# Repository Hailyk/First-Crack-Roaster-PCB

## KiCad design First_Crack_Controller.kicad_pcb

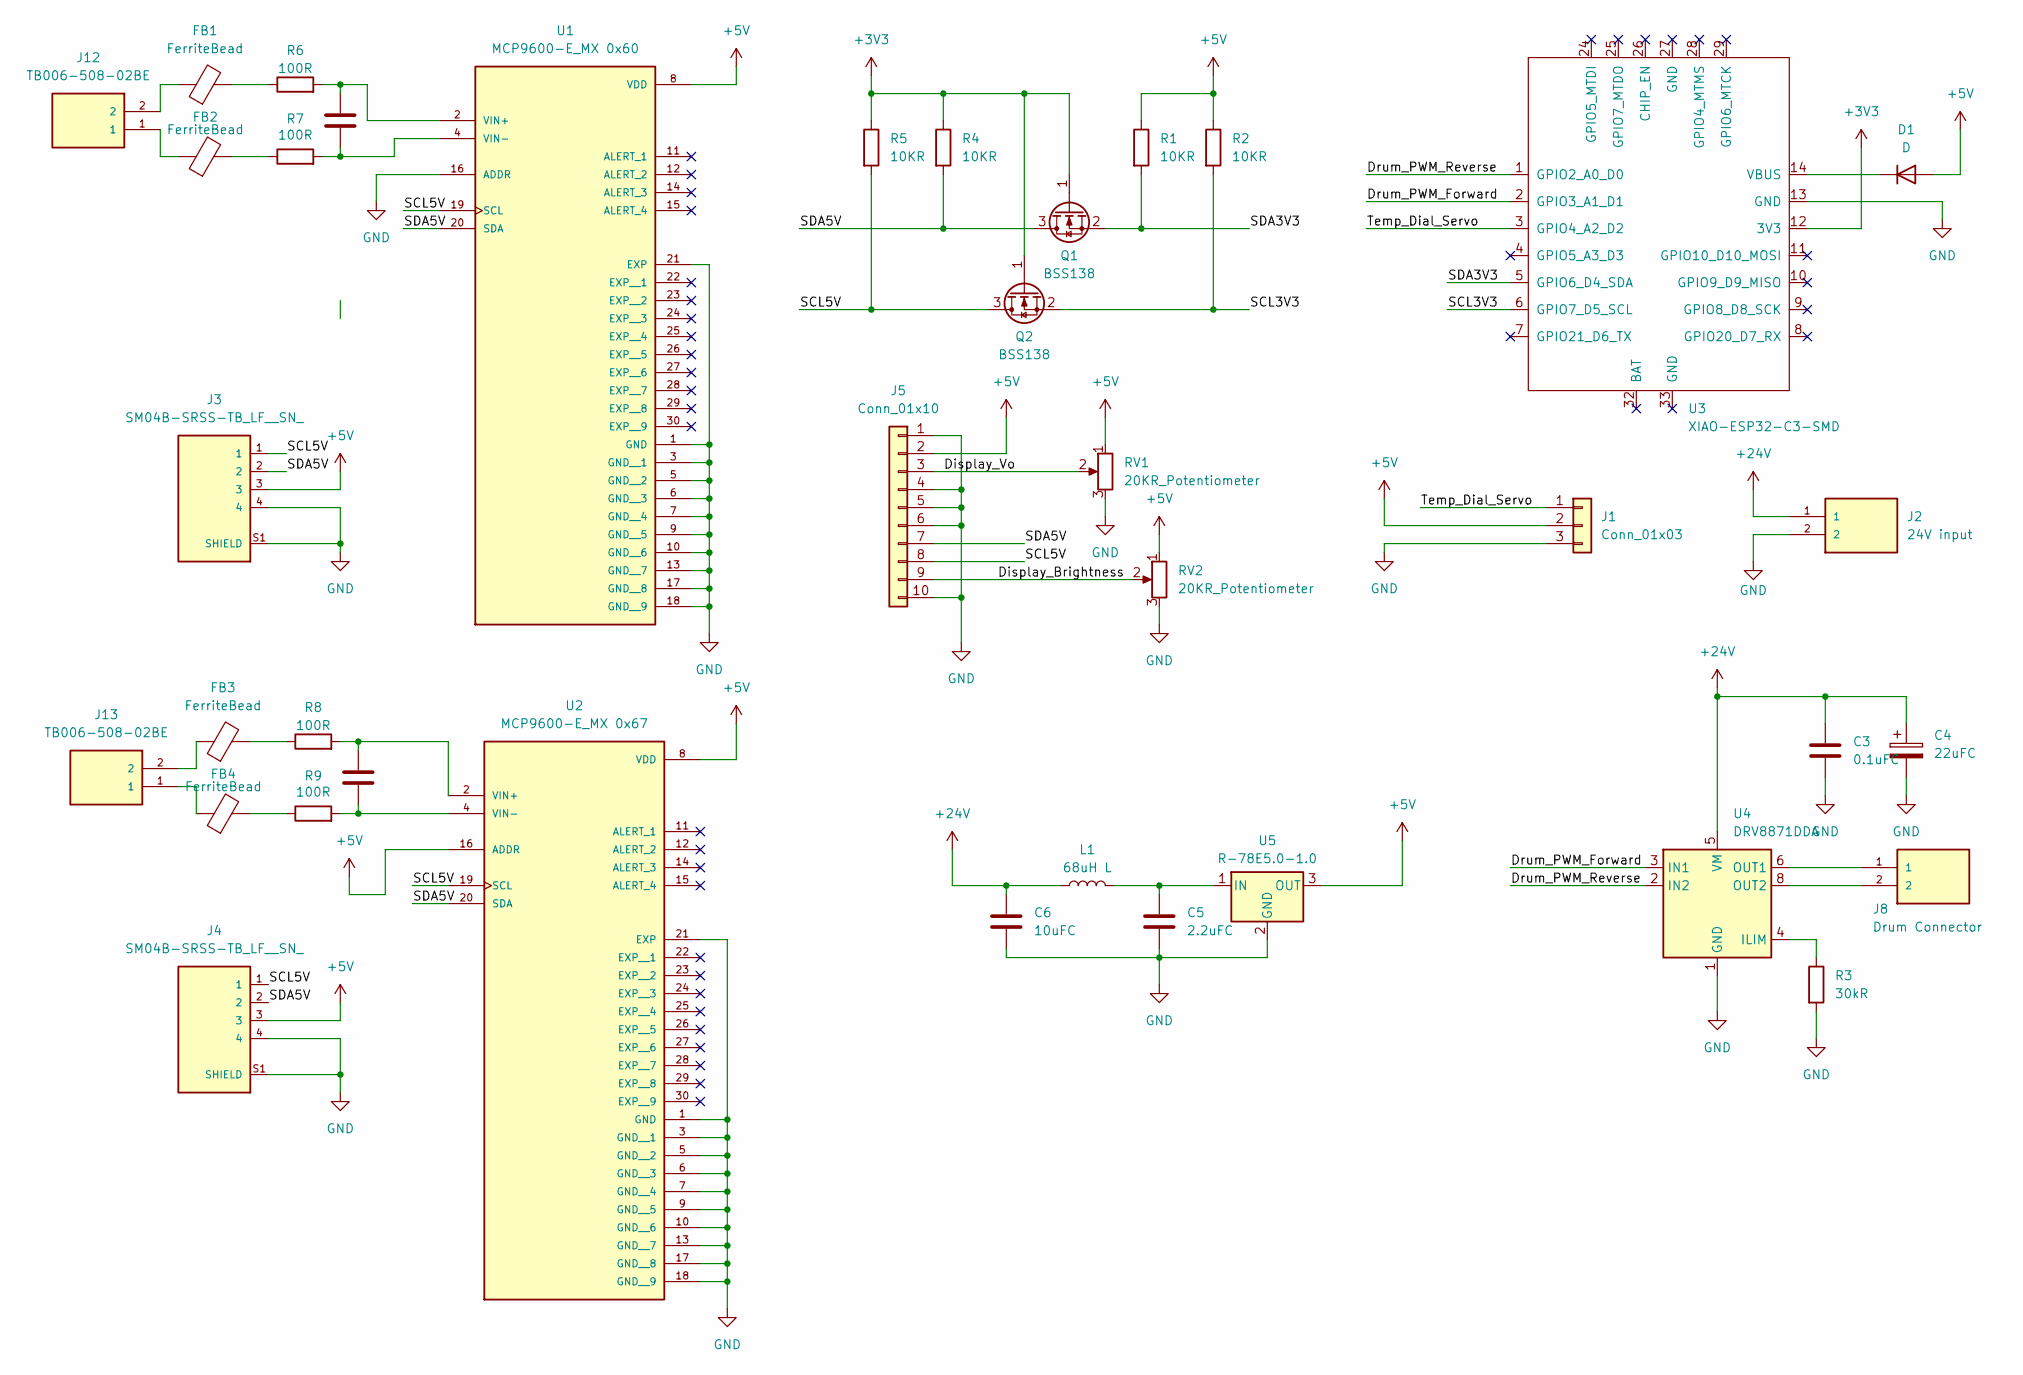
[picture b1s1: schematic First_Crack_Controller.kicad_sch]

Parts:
C1, C2: 0.1uF; C_0805_2012Metric
C3: 0.1uFC; C_0805_2012Metric
C4: 22uFC; C_0805_2012Metric
C5: 2.2uFC; C_0805_2012Metric
C6: 10uFC; C_0805_2012Metric
D1: D; D_0805_2012Metric
FB1, FB2, FB3, FB4: FerriteBead; C_0805_2012Metric
J1: Conn_01x03; PinHeader_1x03_P2.54mm_Vertical
J2: 24V input; CUI_TB006-508-02BE; DigiKey_Part_Number 102-6191-ND
J3, J4: SM04B-SRSS-TB_LF__SN_; JST_SM04B-SRSS-TB_LF__SN_
J5: Conn_01x10; PinHeader_1x10_P2.54mm_Vertical
J8: Drum Connector; CUI_TB006-508-02BE; DigiKey_Part_Number 102-6191-ND
J12, J13: TB006-508-02BE; CUI_TB006-508-02BE; DigiKey_Part_Number 102-6191-ND
L1: 68uH L; L_0805_2012Metric
Q1, Q2: BSS138; SOT-23-3
R1, R2, R4, R5: 10KR; R_0805_2012Metric
R3: 30kR; R_0805_2012Metric
R6, R7, R8, R9: 100R; R_0805_2012Metric
RV1, RV2: 20KR_Potentiometer; Potentiometer_Bourns_3296Y_Vertical
U1: MCP9600-E_MX 0x60; QFN65P500X500X100-21N_MCP9600-E_MX; PARTREV F
U2: MCP9600-E_MX 0x67; QFN65P500X500X100-21N_MCP9600-E_MX; PARTREV F
U3: XIAO-ESP32-C3-SMD
U4: DRV8871DDA; VREG_LM5017MR_NOPB
U5: R-78E5.0-1.0; Converter_DCDC_RECOM_R-78E-0.5_THT

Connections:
+3V3: Q1.1 (G), Q2.1 (G), R4.1, R5.1, U3.12 (3V3)
+5V: D1.2 (A), J1.2, J3.3, J4.3, J5.2, R1.1, R2.1, RV1.1, RV2.1, U1.8 (VDD), U2.8 (VDD), U2.16 (ADDR), U5.3 (OUT)
+24V: C3.1, C4.1, C6.1, J2.1, L1.1, U4.5 (VM)
/Display_Brightness: J5.9, RV2.2
/Display_Vo: J5.3, RV1.2
/Drum_PWM_Forward: U3.2 (GPIO3_A1_D1), U4.3 (IN1)
/Drum_PWM_Reverse: U3.1 (GPIO2_A0_D0), U4.2 (IN2)
/SCL3V3: Q2.2 (S), R2.2, U3.6 (GPIO7_D5_SCL)
/SCL5V: J3.1, J4.1, J5.8, Q2.3 (D), R5.2, U1.19 (SCL), U2.19 (SCL)
/SDA3V3: Q1.2 (S), R1.2, U3.5 (GPIO6_D4_SDA)
/SDA5V: J3.2, J4.2, J5.7, Q1.3 (D), R4.2, U1.20 (SDA), U2.20 (SDA)
/Temp_Dial_Servo: J1.1, U3.3 (GPIO4_A2_D2)
GND: C3.2, C4.2, C5.2, C6.2, J1.3, J2.2, J3.4, J3.S1 (SHIELD), J3.S2 (SHIELD), J4.4, J4.S1 (SHIELD), J4.S2 (SHIELD), J5.1, J5.4, J5.5, J5.6, J5.10, R3.2, RV1.3, RV2.3, U1.1 (GND), U1.3 (GND__1), U1.5 (GND__2), U1.6 (GND__3), U1.7 (GND__4), U1.9 (GND__5), U1.10 (GND__6), U1.13 (GND__7), U1.16 (ADDR), U1.17 (GND__8), U1.18 (GND__9), U1.21 (EXP), U2.1 (GND), U2.3 (GND__1), U2.5 (GND__2), U2.6 (GND__3), U2.7 (GND__4), U2.9 (GND__5), U2.10 (GND__6), U2.13 (GND__7), U2.17 (GND__8), U2.18 (GND__9), U2.21 (EXP), U3.13 (GND), U4.1 (GND), U4.7 (GND), U4.9 (GND), U5.2 (GND)
unnamed: D1.1 (K), U3.14 (VBUS)
unnamed: FB1.1, J12.2
unnamed: FB1.2, R6.1
unnamed: FB2.1, J12.1
unnamed: FB2.2, R7.1
unnamed: FB3.1, J13.2
unnamed: FB3.2, R8.1
unnamed: FB4.1, J13.1
unnamed: FB4.2, R9.1
unnamed: C1.1, R6.2, U1.2 (VIN+)
unnamed: C1.2, R7.2, U1.4 (VIN-)
unnamed: C2.1, R8.2, U2.2 (VIN+)
unnamed: C2.2, R9.2, U2.4 (VIN-)
unnamed: R3.1, U4.4 (ILIM)
unnamed: J8.1, U4.6 (OUT1)
unnamed: J8.2, U4.8 (OUT2)
unnamed: C5.1, L1.2, U5.1 (IN)

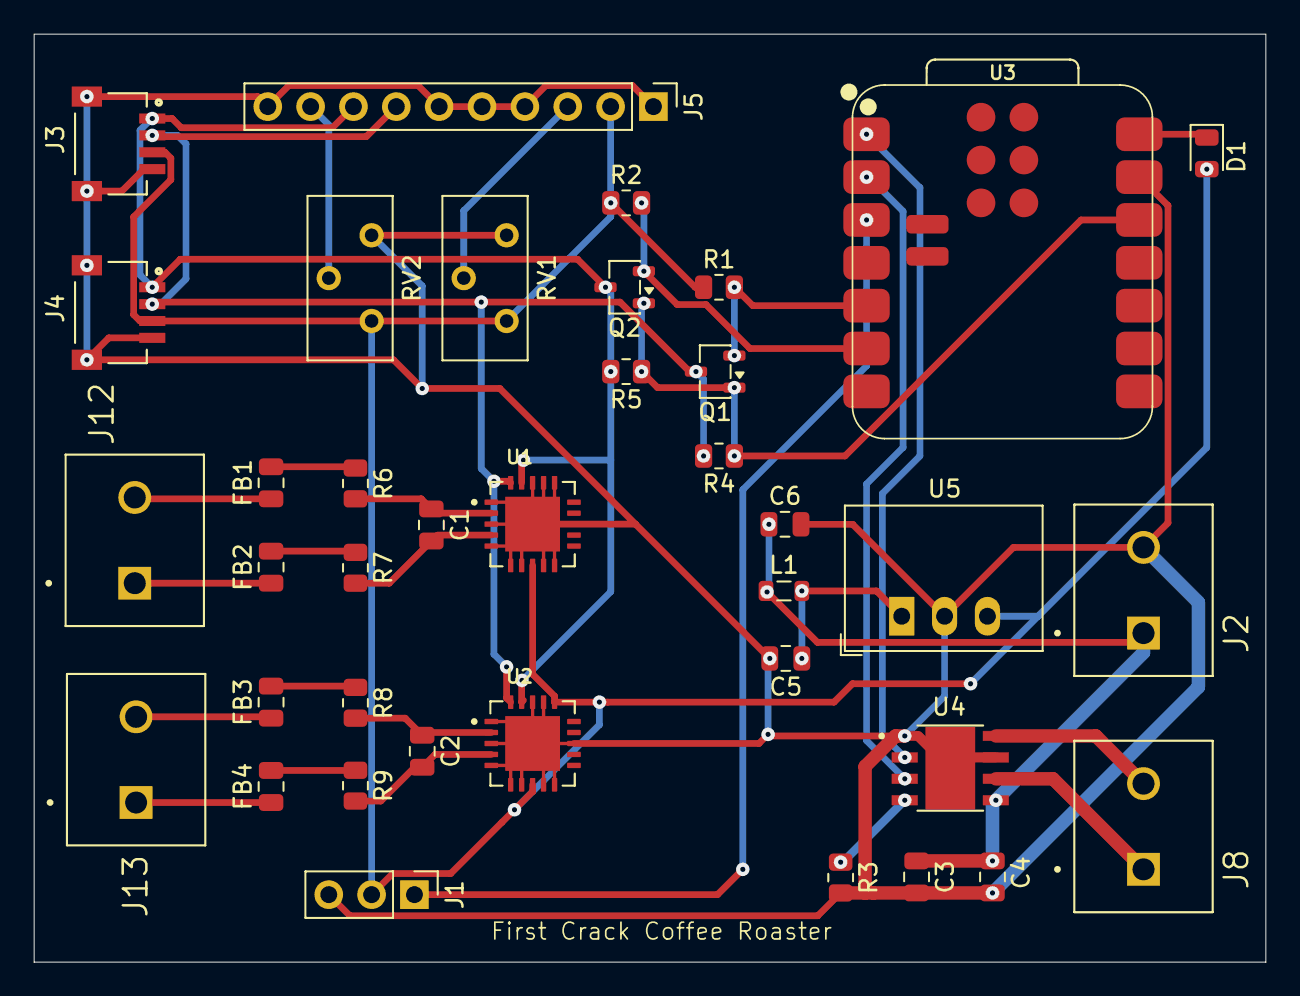
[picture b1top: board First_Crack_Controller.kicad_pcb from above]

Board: 2 copper layers, 73.0 x 55.0 mm, 38 parts (0 on the bottom side), 30 nets.

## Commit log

2026-04-06 changed 10 pin connector
2026-04-06 pcb board
2026-04-07 completed pcb
